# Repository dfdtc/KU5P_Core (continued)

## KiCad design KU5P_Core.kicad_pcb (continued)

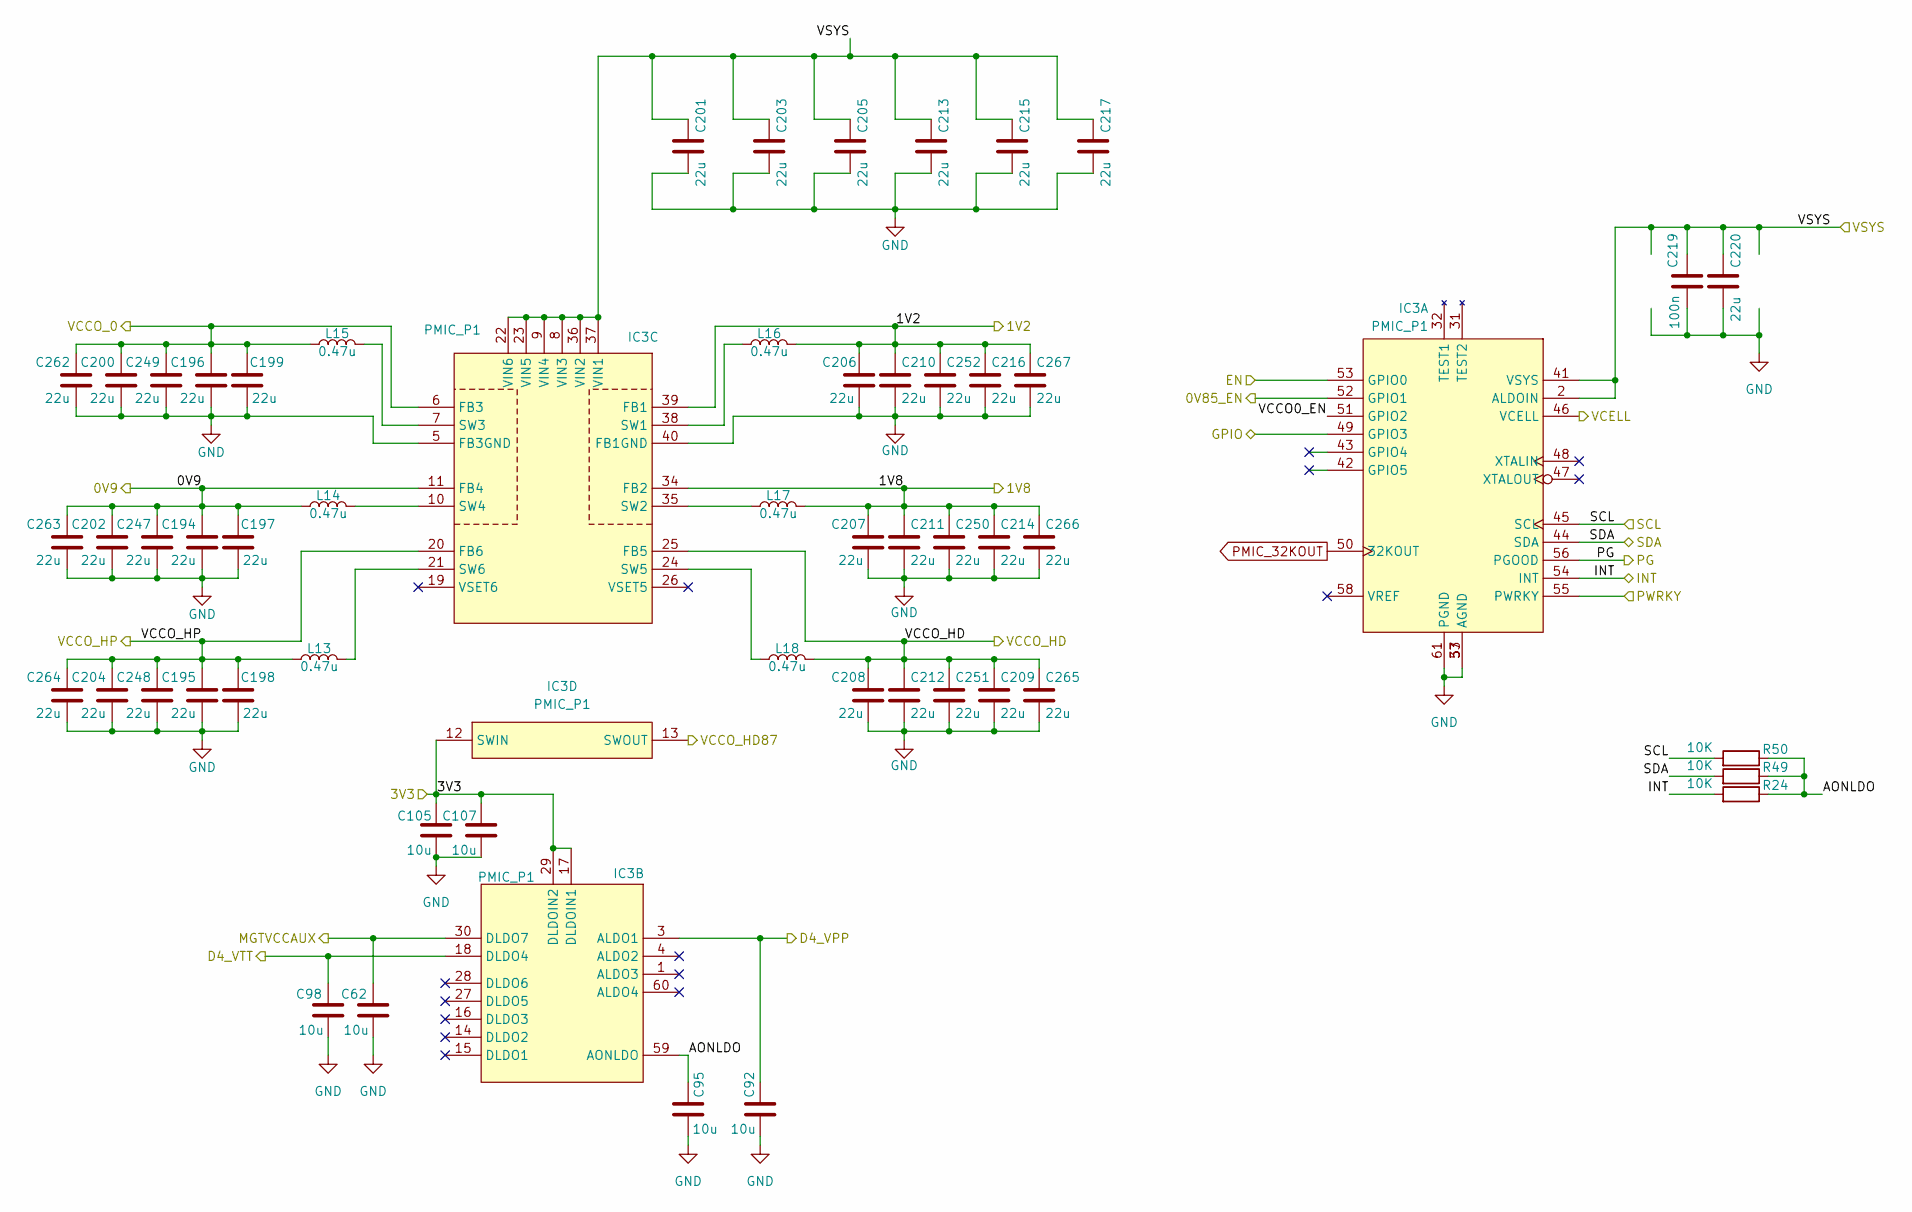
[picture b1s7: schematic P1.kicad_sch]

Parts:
C62, C92, C95, C98, C105, C107: 10u; C_0402_1005Metric
C194, C195, C196, C197, C198, C199, C200, C202, C204, C206, C207, C208, C209, C210, C211, C212, C214, C216, C247, C248, C249, C250, C251, C252, C262, C263, C264, C265, C266, C267: 22u; C_0402_1005Metric
C201, C203, C205, C213, C215, C217, C220: 22u; C_0603_1608Metric
C219: 100n; C_0402_1005Metric
IC3: PMIC_P1; QFN-60-1EP_7x7mm_P0.4mm_EP5.4x5.4mm
L13, L14, L15, L16, L17, L18: 0.47u; L_Changjiang_FTC252012S
R24, R49, R50: 10K; R_0201_0603Metric

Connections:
3V3: C105.1, C107.1, C201.1, C203.1, C205.1, C213.1, C215.1, C217.1, C219.1, C220.1, IC3.2 (ALDOIN), IC3.8 (VIN3), IC3.9 (VIN4), IC3.12 (SWIN), IC3.17 (DLDOIN1), IC3.22 (VIN6), IC3.23 (VIN5), IC3.29 (DLDOIN2), IC3.36 (VIN2), IC3.37 (VIN1), IC3.41 (VSYS); also elsewhere on the board
+1V8: C207.1, C211.1, C214.1, C250.1, C266.1, IC3.34 (FB2), L17.1; also elsewhere on the board
/Power/0.85Vdigi/EN: IC3.52 (GPIO1); also elsewhere on the board
/Power/IN_Rail/PG: IC3.53 (GPIO0); also elsewhere on the board
/Power/P1/AONLDO: C95.1, IC3.59 (AONLDO), R24.1, R49.1, R50.1
/Power/P1/VCCO0_EN: IC3.51 (GPIO2)
D4_VPP: C92.1, IC3.3 (ALDO1); also elsewhere on the board
D4_VTT: C98.1, IC3.18 (DLDO4); also elsewhere on the board
GND: C62.2, C92.2, C95.2, C98.2, C105.2, C107.2, C194.2, C195.2, C196.2, C197.2, C198.2, C199.2, C200.2, C201.2, C202.2, C203.2, C204.2, C205.2, C206.2, C207.2, C208.2, C209.2, C210.2, C211.2, C212.2, C213.2, C214.2, C215.2, C216.2, C217.2, C219.2, C220.2, C247.2, C248.2, C249.2, C250.2, C251.2, C252.2, C262.2, C263.2, C264.2, C265.2, C266.2, C267.2, IC3.5 (FB3GND), IC3.33 (AGND), IC3.40 (FB1GND), IC3.57 (AGND), IC3.61 (PGND); also elsewhere on the board
MGTVCC: C194.1, C197.1, C202.1, C247.1, C263.1, IC3.11 (FB4), L14.1; also elsewhere on the board
MGTVCCAUX: C62.1, IC3.30 (DLDO7); also elsewhere on the board
unnamed: IC3.38 (SW1), L16.2
unnamed: IC3.35 (SW2), L17.2
unnamed: IC3.7 (SW3), L15.2
unnamed: IC3.10 (SW4), L14.2
unnamed: IC3.24 (SW5), L18.2
unnamed: IC3.21 (SW6), L13.2
P1_GPIO: IC3.49 (GPIO3); also elsewhere on the board
P1_INT: IC3.54 (INT), R24.2; also elsewhere on the board
PMIC_32KOUT: IC3.50 (32KOUT); also elsewhere on the board
PMIC_PWRKY: IC3.55 (PWRKY); also elsewhere on the board
Power_SCL: IC3.45 (SCL), R50.2; also elsewhere on the board
Power_SDA: IC3.44 (SDA), R49.2; also elsewhere on the board
SYS_PG: IC3.56 (PGOOD); also elsewhere on the board
VBAT: IC3.46 (VCELL); also elsewhere on the board
VCCO_0: C196.1, C199.1, C200.1, C249.1, C262.1, IC3.6 (FB3), L15.1; also elsewhere on the board
VCCO_HD: C208.1, C209.1, C212.1, C251.1, C265.1, IC3.25 (FB5), L18.1; also elsewhere on the board
VCCO_HD87: IC3.13 (SWOUT); also elsewhere on the board
VCCO_HP: C195.1, C198.1, C204.1, C248.1, C264.1, IC3.20 (FB6), L13.1; also elsewhere on the board

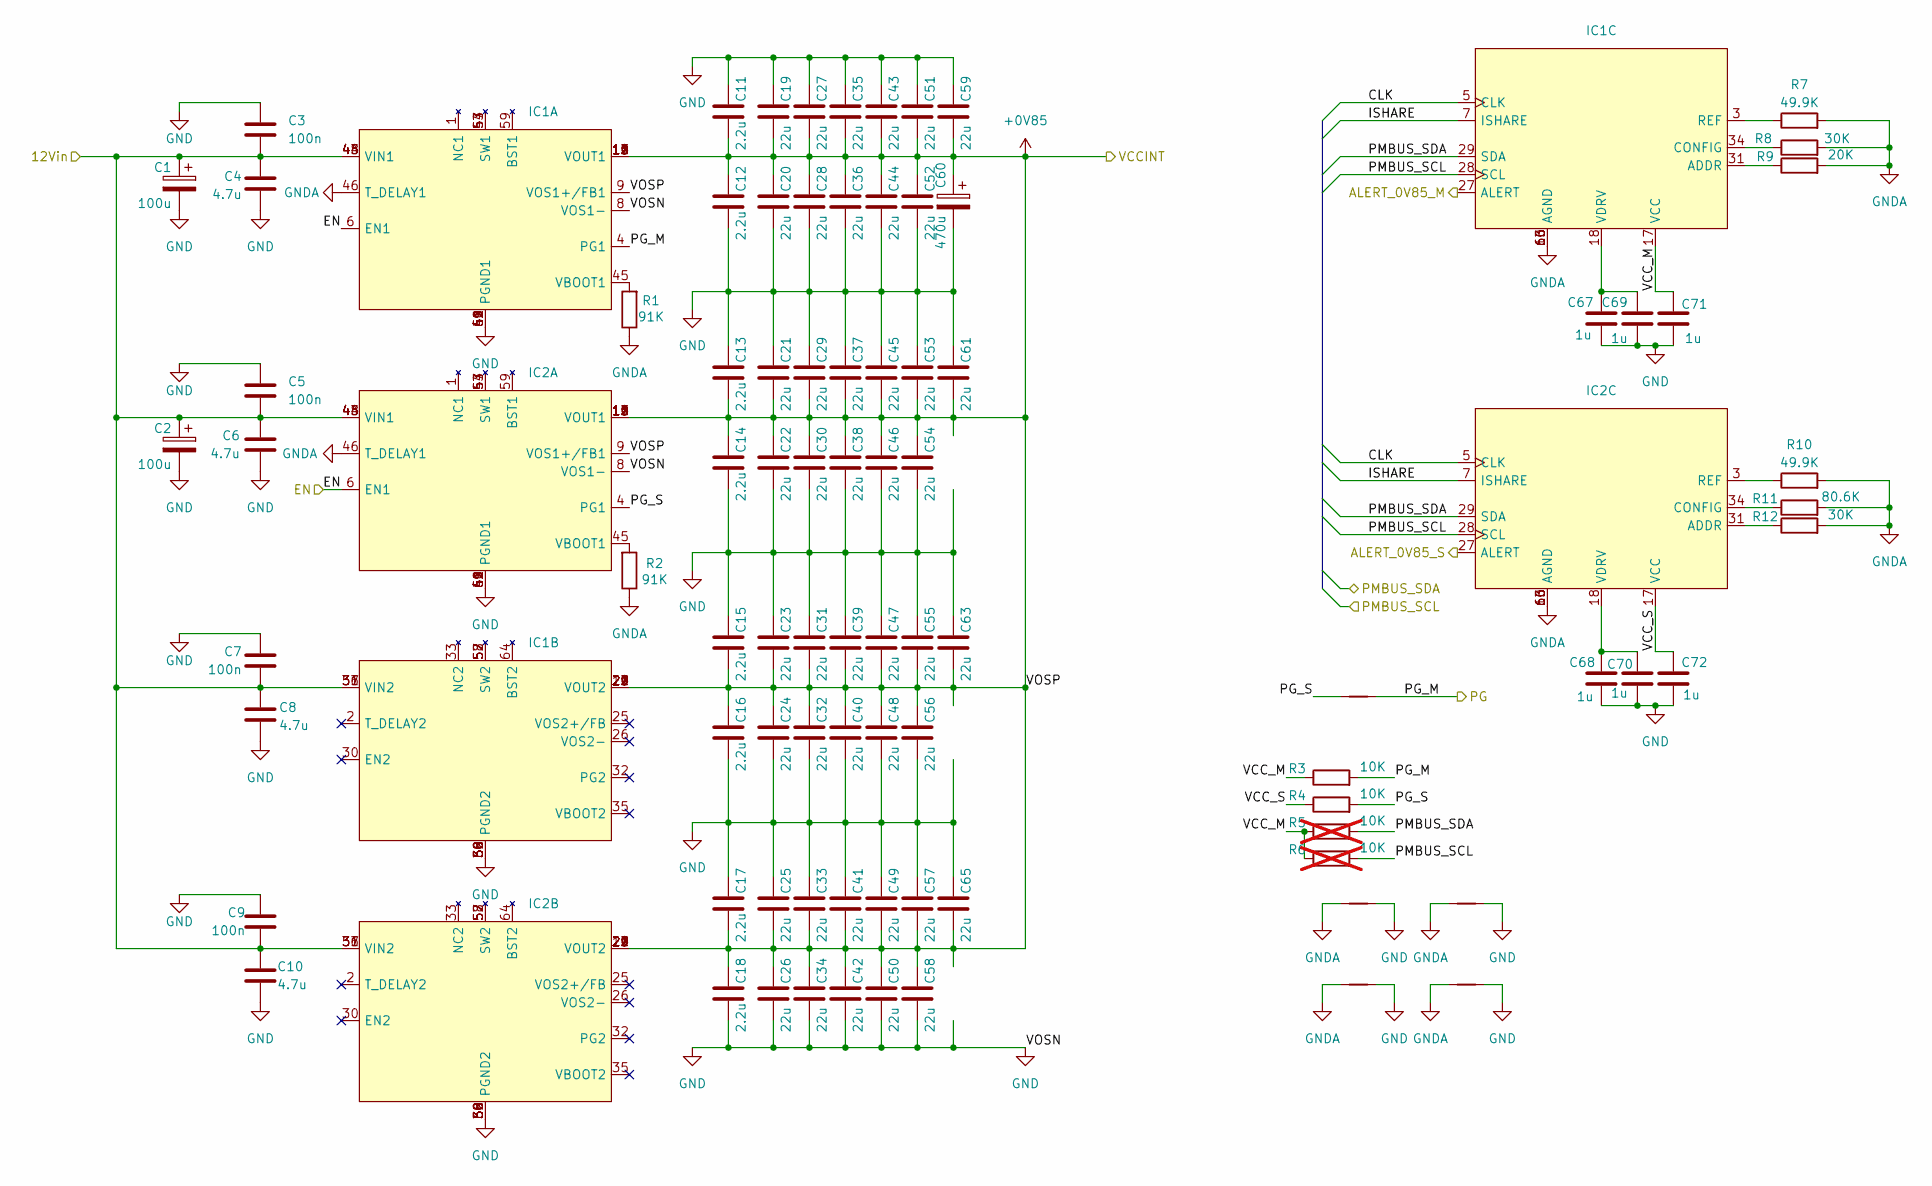
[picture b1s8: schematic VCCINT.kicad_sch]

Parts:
C1, C2: 100u; CP_EIA-7343-20_Kemet-V
C3, C5, C7, C9: 100n; C_0603_1608Metric
C4, C6, C8, C10: 4.7u; C_0603_1608Metric
C11, C12, C13, C14, C15, C16, C17, C18: 2.2u; C_0805_2012Metric
C19, C20, C21, C23, C27, C28, C36, C37, C45, C47, C55, C56, C58, C61: 22u; C_0603_1608Metric
C22, C24, C25, C26, C29, C30, C31, C32, C33, C34, C35, C38, C39, C40, C41, C42, C43, C44, C46, C48, C49, C50, C51, C52, C53, C54, C57, C59, C63, C65: 22u; C_0805_2012Metric
C60: 470u; CP_EIA-7343-20_Kemet-V
C67, C68, C69, C70, C71, C72: 1u; C_0402_1005Metric
IC1, IC2: NDE12D15R-S
NT1, NT2, NT12, NT13, NT14: NetTie_2; NetTie-2_SMD_Pad0.5mm
R1, R2: 91K; R_0201_0603Metric
R3, R4: 10K; R_0201_0603Metric
R5, R6: 10K; R_0201_0603Metric; not fitted
R7, R10: 49.9K; R_0201_0603Metric
R8, R12: 30K; R_0201_0603Metric
R9: 20K; R_0201_0603Metric
R11: 80.6K; R_0201_0603Metric

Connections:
+0V85: C11.2, C12.1, C13.2, C14.1, C15.2, C16.1, C17.2, C18.1, C19.2, C20.1, C21.2, C22.1, C23.2, C24.1, C25.2, C26.1, C27.2, C28.1, C29.2, C30.1, C31.2, C32.1, C33.2, C34.1, C35.2, C36.1, C37.2, C38.1, C39.2, C40.1, C41.2, C42.1, C43.2, C44.1, C45.2, C46.1, C47.2, C48.1, C49.2, C50.1, C51.2, C52.1, C53.2, C54.1, C55.2, C56.1, C57.2, C58.1, C59.2, C60.1, C61.2, C63.2, C65.2, IC1.9 (VOS1+/FB1), IC1.10 (VOUT1), IC1.11 (VOUT1), IC1.12 (VOUT1), IC1.13 (VOUT1), IC1.14 (VOUT1), IC1.15 (VOUT1), IC1.19 (VOUT2), IC1.20 (VOUT2), IC1.21 (VOUT2), IC1.22 (VOUT2), IC1.23 (VOUT2), IC1.24 (VOUT2), IC2.9 (VOS1+/FB1), IC2.10 (VOUT1), IC2.11 (VOUT1), IC2.12 (VOUT1), IC2.13 (VOUT1), IC2.14 (VOUT1), IC2.15 (VOUT1), IC2.19 (VOUT2), IC2.20 (VOUT2), IC2.21 (VOUT2), IC2.22 (VOUT2), IC2.23 (VOUT2), IC2.24 (VOUT2); also elsewhere on the board
+12V: C1.1, C2.1, C3.2, C4.1, C5.2, C6.1, C7.2, C8.1, C9.2, C10.1, IC1.36 (VIN2), IC1.37 (VIN2), IC1.43 (VIN1), IC1.44 (VIN1), IC1.48 (VIN1), IC1.51 (VIN2), IC2.36 (VIN2), IC2.37 (VIN2), IC2.43 (VIN1), IC2.44 (VIN1), IC2.48 (VIN1), IC2.51 (VIN2); also elsewhere on the board
/Power/0.85Vdigi/CLK: IC1.5 (CLK), IC2.5 (CLK)
/Power/0.85Vdigi/EN: IC1.6 (EN1), IC2.6 (EN1); also elsewhere on the board
/Power/0.85Vdigi/ISHARE: IC1.7 (ISHARE), IC2.7 (ISHARE)
/Power/0.85Vdigi/PG_S: IC2.4 (PG1), NT1.1, R4.2
/Power/0.85Vdigi/VCC_M: C71.1, IC1.17 (VCC), R3.1, R5.1, R6.1
/Power/0.85Vdigi/VCC_S: C72.1, IC2.17 (VCC), R4.1
ALERT_M: IC1.27 (ALERT); also elsewhere on the board
ALERT_S: IC2.27 (ALERT); also elsewhere on the board
GND: C1.2, C2.2, C3.1, C4.2, C5.1, C6.2, C7.1, C8.2, C9.1, C10.2, C11.1, C12.2, C13.1, C14.2, C15.1, C16.2, C17.1, C18.2, C19.1, C20.2, C21.1, C22.2, C23.1, C24.2, C25.1, C26.2, C27.1, C28.2, C29.1, C30.2, C31.1, C32.2, C33.1, C34.2, C35.1, C36.2, C37.1, C38.2, C39.1, C40.2, C41.1, C42.2, C43.1, C44.2, C45.1, C46.2, C47.1, C48.2, C49.1, C50.2, C51.1, C52.2, C53.1, C54.2, C55.1, C56.2, C57.1, C58.2, C59.1, C60.2, C61.1, C63.1, C65.1, C67.1, C68.2, C69.2, C70.2, C71.2, C72.2, IC1.8 (VOS1-), IC1.38 (PGND2), IC1.39 (PGND2), IC1.40 (PGND1), IC1.41 (PGND1), IC1.42 (PGND1), IC1.49 (PGND1), IC1.50 (PGND2), IC1.55 (PGND1), IC1.56 (PGND2), IC1.61 (PGND1), IC1.62 (PGND2), IC2.8 (VOS1-), IC2.38 (PGND2), IC2.39 (PGND2), IC2.40 (PGND1), IC2.41 (PGND1), IC2.42 (PGND1), IC2.49 (PGND1), IC2.50 (PGND2), IC2.55 (PGND1), IC2.56 (PGND2), IC2.61 (PGND1), IC2.62 (PGND2), NT2.2, NT12.2, NT13.2, NT14.2; also elsewhere on the board
GNDA: IC1.16 (AGND), IC1.46 (T_DELAY1), IC1.60 (AGND), IC1.63 (AGND), IC2.16 (AGND), IC2.46 (T_DELAY1), IC2.60 (AGND), IC2.63 (AGND), NT2.1, NT12.1, NT13.1, NT14.1, R1.1, R2.1, R7.2, R8.2, R9.2, R10.2, R11.2, R12.2
unnamed: IC1.31 (ADDR), R9.1
unnamed: IC1.34 (CONFIG), R8.1
unnamed: IC1.3 (REF), R7.1
unnamed: C67.2, C69.1, IC1.18 (VDRV)
unnamed: IC1.45 (VBOOT1), R1.2
unnamed: IC2.31 (ADDR), R12.1
unnamed: IC2.34 (CONFIG), R11.1
unnamed: IC2.3 (REF), R10.1
unnamed: C68.1, C70.1, IC2.18 (VDRV)
unnamed: IC2.45 (VBOOT1), R2.2
Power_SCL: IC1.28 (SCL), IC2.28 (SCL), R6.2; also elsewhere on the board
Power_SDA: IC1.29 (SDA), IC2.29 (SDA), R5.2; also elsewhere on the board
SYS_PG: IC1.4 (PG1), NT1.2, R3.2; also elsewhere on the board

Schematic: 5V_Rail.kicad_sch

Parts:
C74: 100u; CP_EIA-7343-20_Kemet-V
C75, C76: 4.7u; C_0603_1608Metric
C77, C78: 100n; C_0603_1608Metric
C79, C80, C81, C82: 2.2u; C_0805_2012Metric
C83, C84, C85, C86, C87, C88, C89, C90: 100u; C_1206_3216Metric
C243, C244, C245: 1u; C_0402_1005Metric
IC5: NDE12D15R-S
NT21: NetTie_2; NetTie-2_SMD_Pad0.5mm
R52: 80.6K; R_0201_0603Metric
R55, R61, R62: 10K; R_0201_0603Metric
R56: 39.2K; R_0201_0603Metric
R57: 121K; R_0201_0603Metric
R58: 140K; R_0201_0603Metric
R59: 30k; R_0201_0603Metric
R60: 10k; R_0201_0603Metric

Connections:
3V3: C79.2, C80.1, C81.2, C82.1, C83.2, C84.1, C85.2, C86.1, C87.2, C88.1, C89.2, C90.1, IC5.9 (VOS1+/FB1), IC5.10 (VOUT1), IC5.11 (VOUT1), IC5.12 (VOUT1), IC5.13 (VOUT1), IC5.14 (VOUT1), IC5.15 (VOUT1), IC5.19 (VOUT2), IC5.20 (VOUT2), IC5.21 (VOUT2), IC5.22 (VOUT2), IC5.23 (VOUT2), IC5.24 (VOUT2); also elsewhere on the board
+12V: C74.1, C75.1, C76.1, C77.1, C78.2, IC5.36 (VIN2), IC5.37 (VIN2), IC5.43 (VIN1), IC5.44 (VIN1), IC5.48 (VIN1), IC5.51 (VIN2), R59.1; also elsewhere on the board
/Power/IN_Rail/EN: IC5.6 (EN1), R59.2, R60.1
/Power/IN_Rail/PG: IC5.4 (PG1), R62.2; also elsewhere on the board
/Power/IN_Rail/POR: IC5.27 (ALERT), R61.2
/Power/IN_Rail/VCC: C245.1, IC5.17 (VCC), R61.1, R62.1
GND: C74.2, C75.2, C76.2, C77.2, C78.1, C79.1, C80.2, C81.1, C82.2, C83.1, C84.2, C85.1, C86.2, C87.1, C88.2, C89.1, C90.2, C243.2, C244.2, C245.2, IC5.8 (VOS1-), IC5.38 (PGND2), IC5.39 (PGND2), IC5.40 (PGND1), IC5.41 (PGND1), IC5.42 (PGND1), IC5.49 (PGND1), IC5.50 (PGND2), IC5.55 (PGND1), IC5.56 (PGND2), IC5.61 (PGND1), IC5.62 (PGND2), NT21.2, R60.2; also elsewhere on the board
GNDA1: IC5.16 (AGND), IC5.60 (AGND), IC5.63 (AGND), NT21.1, R52.1, R55.1, R56.1, R57.1, R58.1
unnamed: IC5.31 (ADDR), R55.2
unnamed: IC5.34 (CONFIG), R56.2
unnamed: IC5.3 (REF), R57.2
unnamed: C243.1, C244.1, IC5.18 (VDRV)
unnamed: IC5.46 (T_DELAY1), R58.2
unnamed: IC5.45 (VBOOT1), R52.2

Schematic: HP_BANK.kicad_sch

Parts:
J7: FX8-140P-SV1; Hirose_FX8-140P-SV_2x70_P0.6mm

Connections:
GND: J7.1, J7.2, J7.11, J7.12, J7.21, J7.22, J7.31, J7.32, J7.41, J7.42, J7.51, J7.52, J7.61, J7.62, J7.67, J7.68, J7.77, J7.78, J7.87, J7.88, J7.97, J7.98, J7.107, J7.108, J7.117, J7.118, J7.127, J7.128, J7.131, J7.132, J7.137, J7.138, J7.139, J7.140; also elsewhere on the board
IO_L1N_T0L_N1_DBC_66_N: J7.6; also elsewhere on the board
IO_L1N_T0L_N1_DBC_67_N: J7.72; also elsewhere on the board
IO_L1P_T0L_N0_DBC_66_P: J7.4; also elsewhere on the board
IO_L1P_T0L_N0_DBC_67_P: J7.70; also elsewhere on the board
IO_L2N_T0L_N3_66_N: J7.10; also elsewhere on the board
IO_L2N_T0L_N3_67_N: J7.76; also elsewhere on the board
IO_L2P_T0L_N2_66_P: J7.8; also elsewhere on the board
IO_L2P_T0L_N2_67_P: J7.74; also elsewhere on the board
IO_L3N_T0L_N5_AD15N_66_N: J7.16; also elsewhere on the board
IO_L3N_T0L_N5_AD15N_67_N: J7.82; also elsewhere on the board
IO_L3P_T0L_N4_AD15P_66_P: J7.14; also elsewhere on the board
IO_L3P_T0L_N4_AD15P_67_P: J7.80; also elsewhere on the board
IO_L4N_T0U_N7_DBC_AD7N_66_N: J7.20; also elsewhere on the board
IO_L4N_T0U_N7_DBC_AD7N_67_N: J7.86; also elsewhere on the board
IO_L4P_T0U_N6_DBC_AD7P_66_P: J7.18; also elsewhere on the board
IO_L4P_T0U_N6_DBC_AD7P_67_P: J7.84; also elsewhere on the board
IO_L5N_T0U_N9_AD14N_66_N: J7.26; also elsewhere on the board
IO_L5N_T0U_N9_AD14N_67_N: J7.92; also elsewhere on the board
IO_L5P_T0U_N8_AD14P_66_P: J7.24; also elsewhere on the board
IO_L5P_T0U_N8_AD14P_67_P: J7.90; also elsewhere on the board
IO_L6N_T0U_N11_AD6N_66_N: J7.30; also elsewhere on the board
IO_L6N_T0U_N11_AD6N_67_N: J7.96; also elsewhere on the board
IO_L6P_T0U_N10_AD6P_66_P: J7.28; also elsewhere on the board
IO_L6P_T0U_N10_AD6P_67_P: J7.94; also elsewhere on the board
IO_L7N_T1L_N1_QBC_AD13N_66_N: J7.36; also elsewhere on the board
IO_L7N_T1L_N1_QBC_AD13N_67_N: J7.102; also elsewhere on the board
IO_L7P_T1L_N0_QBC_AD13P_66_P: J7.34; also elsewhere on the board
IO_L7P_T1L_N0_QBC_AD13P_67_P: J7.100; also elsewhere on the board
IO_L8N_T1L_N3_AD5N_66_N: J7.40; also elsewhere on the board
IO_L8N_T1L_N3_AD5N_67_N: J7.106; also elsewhere on the board
IO_L8P_T1L_N2_AD5P_66_P: J7.38; also elsewhere on the board
IO_L8P_T1L_N2_AD5P_67_P: J7.104; also elsewhere on the board
IO_L9N_T1L_N5_AD12N_66_N: J7.46; also elsewhere on the board
IO_L9N_T1L_N5_AD12N_67_N: J7.112; also elsewhere on the board
IO_L9P_T1L_N4_AD12P_66_P: J7.44; also elsewhere on the board
IO_L9P_T1L_N4_AD12P_67_P: J7.110; also elsewhere on the board
IO_L10N_T1U_N7_QBC_AD4N_66_N: J7.50; also elsewhere on the board
IO_L10N_T1U_N7_QBC_AD4N_67_N: J7.116; also elsewhere on the board
IO_L10P_T1U_N6_QBC_AD4P_66_P: J7.48; also elsewhere on the board
IO_L10P_T1U_N6_QBC_AD4P_67_P: J7.114; also elsewhere on the board
IO_L11N_T1U_N9_GC_66_N: J7.56; also elsewhere on the board
IO_L11N_T1U_N9_GC_67_N: J7.122; also elsewhere on the board
IO_L11P_T1U_N8_GC_66_P: J7.54; also elsewhere on the board
IO_L11P_T1U_N8_GC_67_P: J7.120; also elsewhere on the board
IO_L12N_T1U_N11_GC_66_N: J7.60; also elsewhere on the board
IO_L12N_T1U_N11_GC_67_N: J7.126; also elsewhere on the board
IO_L12P_T1U_N10_GC_66_P: J7.58; also elsewhere on the board
IO_L12P_T1U_N10_GC_67_P: J7.124; also elsewhere on the board
IO_L13N_T2L_N1_GC_QBC_66_N: J7.5; also elsewhere on the board
IO_L13N_T2L_N1_GC_QBC_67_N: J7.71; also elsewhere on the board
IO_L13P_T2L_N0_GC_QBC_66_P: J7.3; also elsewhere on the board
IO_L13P_T2L_N0_GC_QBC_67_P: J7.69; also elsewhere on the board
IO_L14N_T2L_N3_GC_66_N: J7.9; also elsewhere on the board
IO_L14N_T2L_N3_GC_67_N: J7.75; also elsewhere on the board
IO_L14P_T2L_N2_GC_66_P: J7.7; also elsewhere on the board
IO_L14P_T2L_N2_GC_67_P: J7.73; also elsewhere on the board
IO_L15N_T2L_N5_AD11N_66_N: J7.15; also elsewhere on the board
IO_L15N_T2L_N5_AD11N_67_N: J7.81; also elsewhere on the board
IO_L15P_T2L_N4_AD11P_66_P: J7.13; also elsewhere on the board
IO_L15P_T2L_N4_AD11P_67_P: J7.79; also elsewhere on the board
IO_L16N_T2U_N7_QBC_AD3N_66_N: J7.19; also elsewhere on the board
IO_L16N_T2U_N7_QBC_AD3N_67_N: J7.85; also elsewhere on the board
IO_L16P_T2U_N6_QBC_AD3P_66_P: J7.17; also elsewhere on the board
IO_L16P_T2U_N6_QBC_AD3P_67_P: J7.83; also elsewhere on the board
IO_L17N_T2U_N9_AD10N_66_N: J7.25; also elsewhere on the board
IO_L17N_T2U_N9_AD10N_67_N: J7.91; also elsewhere on the board
IO_L17P_T2U_N8_AD10P_66_P: J7.23; also elsewhere on the board
IO_L17P_T2U_N8_AD10P_67_P: J7.89; also elsewhere on the board
IO_L18N_T2U_N11_AD2N_66_N: J7.29; also elsewhere on the board
IO_L18N_T2U_N11_AD2N_67_N: J7.95; also elsewhere on the board
IO_L18P_T2U_N10_AD2P_66_P: J7.27; also elsewhere on the board
IO_L18P_T2U_N10_AD2P_67_P: J7.93; also elsewhere on the board
IO_L19N_T3L_N1_DBC_AD9N_66_N: J7.35; also elsewhere on the board
IO_L19N_T3L_N1_DBC_AD9N_67_N: J7.101; also elsewhere on the board
IO_L19P_T3L_N0_DBC_AD9P_66_P: J7.33; also elsewhere on the board
IO_L19P_T3L_N0_DBC_AD9P_67_P: J7.99; also elsewhere on the board
IO_L20N_T3L_N3_AD1N_66_N: J7.39; also elsewhere on the board
IO_L20N_T3L_N3_AD1N_67_N: J7.105; also elsewhere on the board
IO_L20P_T3L_N2_AD1P_66_P: J7.37; also elsewhere on the board
IO_L20P_T3L_N2_AD1P_67_P: J7.103; also elsewhere on the board
IO_L21N_T3L_N5_AD8N_66_N: J7.45; also elsewhere on the board
IO_L21N_T3L_N5_AD8N_67_N: J7.111; also elsewhere on the board
IO_L21P_T3L_N4_AD8P_66_P: J7.43; also elsewhere on the board
IO_L21P_T3L_N4_AD8P_67_P: J7.109; also elsewhere on the board
IO_L22N_T3U_N7_DBC_AD0N_66_N: J7.49; also elsewhere on the board
IO_L22N_T3U_N7_DBC_AD0N_67_N: J7.115; also elsewhere on the board
IO_L22P_T3U_N6_DBC_AD0P_66_P: J7.47; also elsewhere on the board
IO_L22P_T3U_N6_DBC_AD0P_67_P: J7.113; also elsewhere on the board
IO_L23N_T3U_N9_66_N: J7.55; also elsewhere on the board
IO_L23N_T3U_N9_67_N: J7.121; also elsewhere on the board
IO_L23P_T3U_N8_66_P: J7.53; also elsewhere on the board
IO_L23P_T3U_N8_67_P: J7.119; also elsewhere on the board
IO_L24N_T3U_N11_66_N: J7.59; also elsewhere on the board
IO_L24N_T3U_N11_67_N: J7.125; also elsewhere on the board
IO_L24P_T3U_N10_66_P: J7.57; also elsewhere on the board
IO_L24P_T3U_N10_67_P: J7.123; also elsewhere on the board
IO_T1U_N12_66: J7.64; also elsewhere on the board
IO_T1U_N12_67: J7.65; also elsewhere on the board
IO_T2U_N12_66: J7.66; also elsewhere on the board
IO_T2U_N12_67: J7.130; also elsewhere on the board
IO_T3U_N12_66: J7.63; also elsewhere on the board
IO_T3U_N12_67: J7.129; also elsewhere on the board
VCCO_HP: J7.133, J7.135; also elsewhere on the board

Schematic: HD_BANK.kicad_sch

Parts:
J6: FX8-140P-SV1; Hirose_FX8-140P-SV_2x70_P0.6mm

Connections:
+12V: J6.123, J6.124, J6.125, J6.126, J6.127, J6.128, J6.129, J6.130, J6.131, J6.132, J6.133, J6.134, J6.135, J6.136, J6.137, J6.138, J6.139, J6.140; also elsewhere on the board
FAN_PWM: J6.87; also elsewhere on the board
FAN_TACH: J6.89; also elsewhere on the board
GND: J6.1, J6.2, J6.11, J6.12, J6.21, J6.22, J6.31, J6.32, J6.41, J6.42, J6.51, J6.52, J6.61, J6.62, J6.71, J6.72, J6.77, J6.78, J6.81, J6.82, J6.91, J6.92, J6.97, J6.98, J6.99, J6.100, J6.101, J6.102, J6.103, J6.104, J6.105, J6.106, J6.107, J6.108, J6.109, J6.110, J6.111, J6.112, J6.113, J6.114, J6.115, J6.116, J6.117, J6.118, J6.119, J6.120, J6.121, J6.122; also elsewhere on the board
IO_L1N_AD11N_84_N: J6.5; also elsewhere on the board
IO_L1N_AD11N_86_N: J6.6; also elsewhere on the board
IO_L1P_AD11P_84_P: J6.3; also elsewhere on the board
IO_L1P_AD11P_86_P: J6.4; also elsewhere on the board
IO_L2N_AD10N_84_N: J6.9; also elsewhere on the board
IO_L2N_AD10N_86_N: J6.10; also elsewhere on the board
IO_L2P_AD10P_84_P: J6.7; also elsewhere on the board
IO_L2P_AD10P_86_P: J6.8; also elsewhere on the board
IO_L3N_AD9N_84_N: J6.15; also elsewhere on the board
IO_L3N_AD9N_86_N: J6.16; also elsewhere on the board
IO_L3P_AD9P_84_P: J6.13; also elsewhere on the board
IO_L3P_AD9P_86_P: J6.14; also elsewhere on the board
IO_L4N_AD8N_84_N: J6.19; also elsewhere on the board
IO_L4N_AD8N_86_N: J6.20; also elsewhere on the board
IO_L4P_AD8P_84_P: J6.17; also elsewhere on the board
IO_L4P_AD8P_86_P: J6.18; also elsewhere on the board
IO_L5N_HDGC_AD7N_84_N: J6.25; also elsewhere on the board
IO_L5N_HDGC_AD7N_86_N: J6.26; also elsewhere on the board
IO_L5P_HDGC_AD7P_84_P: J6.23; also elsewhere on the board
IO_L5P_HDGC_AD7P_86_P: J6.24; also elsewhere on the board
IO_L6N_HDGC_87_N: J6.86; also elsewhere on the board
IO_L6N_HDGC_AD6N_84_N: J6.29; also elsewhere on the board
IO_L6N_HDGC_AD6N_86_N: J6.30; also elsewhere on the board
IO_L6P_HDGC_AD6P_84_P: J6.27; also elsewhere on the board
IO_L6P_HDGC_AD6P_86_P: J6.28; also elsewhere on the board
IO_L7N_HDGC_87_N: J6.66; also elsewhere on the board
IO_L7N_HDGC_AD5N_84_N: J6.35; also elsewhere on the board
IO_L7N_HDGC_AD5N_86_N: J6.36; also elsewhere on the board
IO_L7P_HDGC_87_P: J6.64; also elsewhere on the board
IO_L7P_HDGC_AD5P_84_P: J6.33; also elsewhere on the board
IO_L7P_HDGC_AD5P_86_P: J6.34; also elsewhere on the board
IO_L8N_HDGC_87_N: J6.70; also elsewhere on the board
IO_L8N_HDGC_AD4N_84_N: J6.39; also elsewhere on the board
IO_L8N_HDGC_AD4N_86_N: J6.40; also elsewhere on the board
IO_L8P_HDGC_87_P: J6.68; also elsewhere on the board
IO_L8P_HDGC_AD4P_84_P: J6.37; also elsewhere on the board
IO_L8P_HDGC_AD4P_86_P: J6.38; also elsewhere on the board
IO_L9N_AD3N_84_N: J6.45; also elsewhere on the board
IO_L9N_AD3N_86_N: J6.46; also elsewhere on the board
IO_L9N_AD11N_87_N: J6.76; also elsewhere on the board
IO_L9P_AD3P_84_P: J6.43; also elsewhere on the board
IO_L9P_AD3P_86_P: J6.44; also elsewhere on the board
IO_L9P_AD11P_87_P: J6.74; also elsewhere on the board
IO_L10N_AD2N_84_N: J6.49; also elsewhere on the board
IO_L10N_AD2N_86_N: J6.50; also elsewhere on the board
IO_L10N_AD10N_87_N: J6.65; also elsewhere on the board
IO_L10P_AD2P_84_P: J6.47; also elsewhere on the board
IO_L10P_AD2P_86_P: J6.48; also elsewhere on the board
IO_L10P_AD10P_87_P: J6.63; also elsewhere on the board
IO_L11N_AD1N_84_N: J6.55; also elsewhere on the board
IO_L11N_AD1N_86_N: J6.56; also elsewhere on the board
IO_L11N_AD9N_87_N: J6.69; also elsewhere on the board
IO_L11P_AD1P_84_P: J6.53; also elsewhere on the board
IO_L11P_AD1P_86_P: J6.54; also elsewhere on the board
IO_L11P_AD9P_87_P: J6.67; also elsewhere on the board
IO_L12N_AD0N_84_N: J6.59; also elsewhere on the board
IO_L12N_AD0N_86_N: J6.60; also elsewhere on the board
IO_L12N_AD8N_87_N: J6.75; also elsewhere on the board
IO_L12P_AD0P_84_P: J6.57; also elsewhere on the board
IO_L12P_AD0P_86_P: J6.58; also elsewhere on the board
IO_L12P_AD8P_87_P: J6.73; also elsewhere on the board
P1_GPIO: J6.85; also elsewhere on the board
P1_INT: J6.83; also elsewhere on the board
PMIC_32KOUT: J6.84; also elsewhere on the board
PMIC_PWRKY: J6.94; also elsewhere on the board
PROGRAM_B_0: J6.93; also elsewhere on the board
Power_SCL: J6.90; also elsewhere on the board
Power_SDA: J6.88; also elsewhere on the board
SYS_PG: J6.95; also elsewhere on the board
VBAT: J6.96; also elsewhere on the board
VCCO_HD: J6.79, J6.80; also elsewhere on the board

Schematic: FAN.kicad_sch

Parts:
C73, C106: 220U; CP_EIA-7343-31_Kemet-D; not fitted
J4: XH 2.54; JST_XA_B02B-XASK-1_1x02_P2.50mm_Vertical; not fitted
M1: Fan_4pin; FanPinHeader_1x04_P2.54mm_Vertical; not fitted
Q1: DMN2040U; SOT-23; not fitted
R45: 10K; R_0201_0603Metric; not fitted

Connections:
unnamed: C73.1, M1.2 (+)
unnamed: C106.1, J4.2
unnamed: C73.2, C106.2, J4.1, M1.1 (-), Q1.2 (S), R45.2
unnamed: M1.4 (PWM), Q1.3 (D)
unnamed: Q1.1 (G), R45.1

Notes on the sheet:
Intel 4Pin Fan

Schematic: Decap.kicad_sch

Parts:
C133, C155: 330u; C_1210_3225Metric
C134, C156, C157, C158: 100u; C_0805_2012Metric
C135, C147, C148, C149, C150, C151, C152, C153, C154, C159: 47u; C_0603_1608Metric
C136, C140, C141, C142, C143, C144, C145, C146, C160, C171: 10u; C_0402_1005Metric
C137, C138, C139: 4.7u; C_0201_0603Metric

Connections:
+0V85: C133.1, C134.1, C135.1, C136.1, C140.1, C141.1, C142.1, C143.1, C147.1, C148.1, C149.1, C150.1, C155.1, C156.1, C157.1, C158.1, C171.1; also elsewhere on the board
+1V8: C144.1, C151.1, C152.1; also elsewhere on the board
GND: C133.2, C134.2, C135.2, C136.2, C137.2, C138.2, C139.2, C140.2, C141.2, C142.2, C143.2, C144.2, C145.2, C146.2, C147.2, C148.2, C149.2, C150.2, C151.2, C152.2, C153.2, C154.2, C155.2, C156.2, C157.2, C158.2, C159.2, C160.2, C171.2; also elsewhere on the board
MGTVCC: C137.1; also elsewhere on the board
MGTVCCAUX: C138.1; also elsewhere on the board
VCCO_0: C159.1, C160.1; also elsewhere on the board
VCCO_HD: C145.1, C153.1; also elsewhere on the board
VCCO_HP: C146.1, C154.1; also elsewhere on the board

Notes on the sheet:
VCCO_0

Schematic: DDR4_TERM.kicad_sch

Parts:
C177, C178, C179, C180, C181, C182, C183, C184, C185, C186, C187, C188, C189, C190, C191, C192, C193, C222, C223, C224, C225, C226, C227, C228, C229, C230, C233: 100n; C_0201_0603Metric
C231: 10n; C_0201_0603Metric
R14, R15, R16, R17, R18, R19, R20, R21, R22, R68, R69, R70, R71, R72, R73, R74, R75, R76, R77, R78, R79, R80, R81, R82, R83, R85, R86: 39; R_0201_0603Metric
R41: 10k; R_0201_0603Metric

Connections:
D4.BA0: C193.1, R76.2; also elsewhere on the board
D4.BA1: C222.1, R77.2; also elsewhere on the board
D4.BG0: C233.1, R78.2; also elsewhere on the board
D4.CKE: C227.1, R83.2; also elsewhere on the board
D4.CK_c: C230.1, R86.2; also elsewhere on the board
D4.CK_t: C228.1, R85.2; also elsewhere on the board
D4.ODT: C226.1, R82.2; also elsewhere on the board
D4.PAR: C225.1, R81.2; also elsewhere on the board
D4.~ACT: C223.1, R79.2; also elsewhere on the board
D4.~CS: C224.1, R80.2; also elsewhere on the board
D4.~RST: R41.1; also elsewhere on the board
D4_ADDR0: C177.1, R14.2; also elsewhere on the board
D4_ADDR1: C178.1, R15.2; also elsewhere on the board
D4_ADDR2: C179.1, R16.2; also elsewhere on the board
D4_ADDR3: C180.1, R17.2; also elsewhere on the board
D4_ADDR4: C181.1, R18.2; also elsewhere on the board
D4_ADDR5: C182.1, R19.2; also elsewhere on the board
D4_ADDR6: C183.1, R20.2; also elsewhere on the board
D4_ADDR7: C184.1, R21.2; also elsewhere on the board
D4_ADDR8: C185.1, R22.2; also elsewhere on the board
D4_ADDR9: C186.1, R68.2; also elsewhere on the board
D4_ADDR10: C187.1, R69.2; also elsewhere on the board
D4_ADDR11: C188.1, R70.2; also elsewhere on the board
D4_ADDR12: C189.1, R71.2; also elsewhere on the board
D4_ADDR13: C190.1, R72.2; also elsewhere on the board
D4_ADDR14: C191.1, R73.2; also elsewhere on the board
D4_ADDR15: C192.1, R74.2; also elsewhere on the board
D4_ADDR16: C229.1, R75.2; also elsewhere on the board
D4_VTT: R14.1, R15.1, R16.1, R17.1, R18.1, R19.1, R20.1, R21.1, R22.1, R68.1, R69.1, R70.1, R71.1, R72.1, R73.1, R74.1, R75.1, R76.1, R77.1, R78.1, R79.1, R80.1, R81.1, R82.1, R83.1; also elsewhere on the board
GND: C177.2, C178.2, C179.2, C180.2, C181.2, C182.2, C183.2, C184.2, C185.2, C186.2, C187.2, C188.2, C189.2, C190.2, C191.2, C192.2, C193.2, C222.2, C223.2, C224.2, C225.2, C226.2, C227.2, C228.2, C229.2, C230.2, C233.2, R41.2; also elsewhere on the board
unnamed: C231.2, R85.1, R86.1

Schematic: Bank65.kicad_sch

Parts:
R48: 240; R_0201_0603Metric
U1: XCKU5P-FFVB676; Xilinx_FFG676

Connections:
/FPGA/IO/HP_BANK/Bank65/VRP: R48.1, U1.W21 (IO_T0U_N12_VRP_A28_65)
D4a.LDQS_c: U1.V22 (IO_L4N_T0U_N7_DBC_AD7N_A25_65_N); also elsewhere on the board
D4a.LDQS_t: U1.V21 (IO_L4P_T0U_N6_DBC_AD7P_A24_65_P); also elsewhere on the board
D4a.UDQS_c: U1.W26 (IO_L10N_T1U_N7_QBC_AD4N_A13_D29_65_N); also elsewhere on the board
D4a.UDQS_t: U1.W25 (IO_L10P_T1U_N6_QBC_AD4P_A12_D28_65_P); also elsewhere on the board
D4a.~LDBI: U1.U19 (IO_L1P_T0L_N0_DBC_RS0_65_P); also elsewhere on the board
D4a.~UDBI: U1.Y22 (IO_L7P_T1L_N0_QBC_AD13P_A18_65_P); also elsewhere on the board
D4a_DQ0: U1.T25 (IO_L14P_T2L_N2_GC_A04_D20_65_P); also elsewhere on the board
D4a_DQ1: U1.U25 (IO_L14N_T2L_N3_GC_A05_D21_65_N); also elsewhere on the board
D4a_DQ2: U1.N24 (IO_L15P_T2L_N4_AD11P_A02_D18_65_P); also elsewhere on the board
D4a_DQ3: U1.P24 (IO_L15N_T2L_N5_AD11N_A03_D19_65_N); also elsewhere on the board
D4a_DQ4: U1.P25 (IO_L17P_T2U_N8_AD10P_D14_65_P); also elsewhere on the board
D4a_DQ5: U1.P26 (IO_L17N_T2U_N9_AD10N_D15_65_N); also elsewhere on the board
D4a_DQ6: U1.R25 (IO_L18P_T2U_N10_AD2P_D12_65_P); also elsewhere on the board
D4a_DQ7: U1.R26 (IO_L18N_T2U_N11_AD2N_D13_65_N); also elsewhere on the board
D4a_DQ8: U1.P20 (IO_L20P_T3L_N2_AD1P_D08_65_P); also elsewhere on the board
D4a_DQ9: U1.P21 (IO_L20N_T3L_N3_AD1N_D09_65_N); also elsewhere on the board
D4a_DQ10: U1.R20 (IO_L21P_T3L_N4_AD8P_D06_65_P); also elsewhere on the board
D4a_DQ11: U1.R21 (IO_L21N_T3L_N5_AD8N_D07_65_N); also elsewhere on the board
D4a_DQ12: U1.N19 (IO_L23P_T3U_N8_I2C_SCLK_65_P); also elsewhere on the board
D4a_DQ13: U1.P19 (IO_L23N_T3U_N9_PERSTN1_I2C_SDA_65_N); also elsewhere on the board
D4a_DQ14: U1.N21 (IO_L24P_T3U_N10_EMCCLK_65_P); also elsewhere on the board
D4a_DQ15: U1.N22 (IO_L24N_T3U_N11_DOUT_CSO_B_65_N); also elsewhere on the board
D4b.LDQS_c: U1.V26 (IO_L16N_T2U_N7_QBC_AD3N_A01_D17_65_N); also elsewhere on the board
D4b.LDQS_t: U1.U26 (IO_L16P_T2U_N6_QBC_AD3P_A00_D16_65_P); also elsewhere on the board
D4b.UDQS_c: U1.P23 (IO_L22N_T3U_N7_DBC_AD0N_D05_65_N); also elsewhere on the board
D4b.UDQS_t: U1.N23 (IO_L22P_T3U_N6_DBC_AD0P_D04_65_P); also elsewhere on the board
D4b.~LDBI: U1.T24 (IO_L13P_T2L_N0_GC_QBC_A06_D22_65_P); also elsewhere on the board
D4b.~UDBI: U1.R22 (IO_L19P_T3L_N0_DBC_AD9P_D10_65_P); also elsewhere on the board
D4b_DQ0: U1.U21 (IO_L2P_T0L_N2_FOE_B_65_P); also elsewhere on the board
D4b_DQ1: U1.U22 (IO_L2N_T0L_N3_FWE_FCS2_B_65_N); also elsewhere on the board
D4b_DQ2: U1.T20 (IO_L3P_T0L_N4_AD15P_A26_65_P); also elsewhere on the board
D4b_DQ3: U1.U20 (IO_L3N_T0L_N5_AD15N_A27_65_N); also elsewhere on the board
D4b_DQ4: U1.T22 (IO_L5P_T0U_N8_AD14P_A22_65_P); also elsewhere on the board
D4b_DQ5: U1.T23 (IO_L5N_T0U_N9_AD14N_A23_65_N); also elsewhere on the board
D4b_DQ6: U1.W19 (IO_L6P_T0U_N10_AD6P_A20_65_P); also elsewhere on the board
D4b_DQ7: U1.W20 (IO_L6N_T0U_N11_AD6N_A21_65_N); also elsewhere on the board
D4b_DQ8: U1.Y25 (IO_L8P_T1L_N2_AD5P_A16_65_P); also elsewhere on the board
D4b_DQ9: U1.Y26 (IO_L8N_T1L_N3_AD5N_A17_65_N); also elsewhere on the board
D4b_DQ10: U1.AA24 (IO_L9P_T1L_N4_AD12P_A14_D30_65_P); also elsewhere on the board
D4b_DQ11: U1.AA25 (IO_L9N_T1L_N5_AD12N_A15_D31_65_N); also elsewhere on the board
D4b_DQ12: U1.V23 (IO_L11P_T1U_N8_GC_A10_D26_65_P); also elsewhere on the board
D4b_DQ13: U1.W23 (IO_L11N_T1U_N9_GC_A11_D27_65_N); also elsewhere on the board
D4b_DQ14: U1.V24 (IO_L12P_T1U_N10_GC_A08_D24_65_P); also elsewhere on the board
D4b_DQ15: U1.W24 (IO_L12N_T1U_N11_GC_A09_D25_65_N); also elsewhere on the board
GND: R48.2; also elsewhere on the board
